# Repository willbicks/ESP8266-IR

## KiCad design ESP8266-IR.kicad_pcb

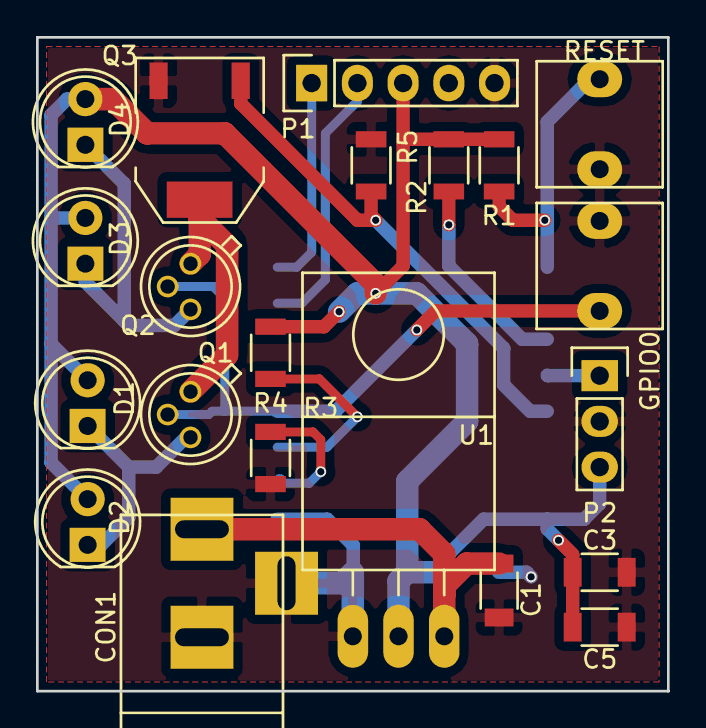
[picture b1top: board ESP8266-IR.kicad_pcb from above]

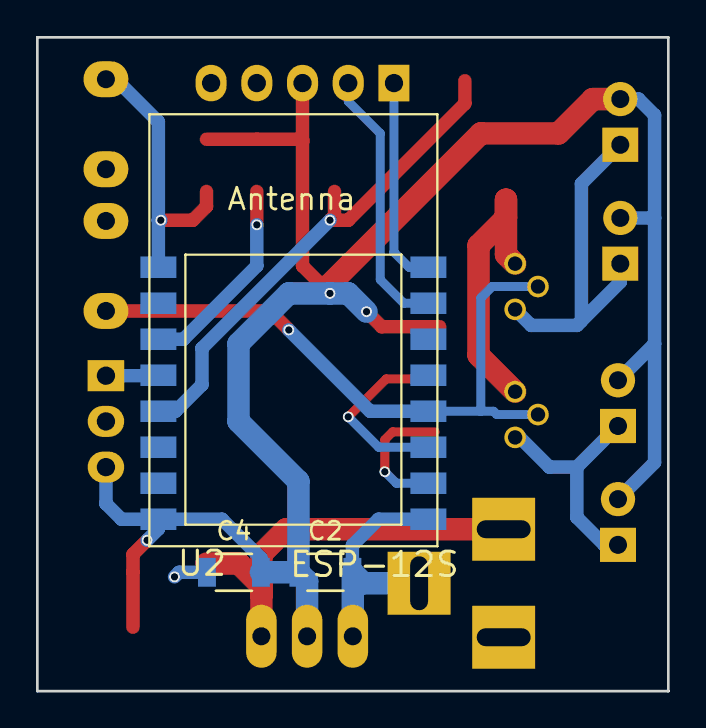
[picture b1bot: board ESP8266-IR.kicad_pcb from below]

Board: 2 copper layers, 35.1 x 36.3 mm, 24 parts (3 on the bottom side), 15 nets.

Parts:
C1, C2, C4: 10uF; C_1206
C3, C5: C; C_1206
CON1: BARREL_JACK
D1, D2, D3, D4: LED; LED-5MM
GPIO0: SW_PUSH; PushbuttonSquare2pin
P1: CONN_01X05; Pin_Header_Straight_1x05
P2: TSOP38238; Pin_Header_Straight_1x03
Q1, Q2: 2N2222A; TO-18_3Pin
Q3: Q_NMOS_GDS; SOT-223
R1, R2, R3, R4, R5: 10k; R_1206
RESET: SW_PUSH; PushbuttonSquare2pin
U1: LD1117S33TR; TO-220_Neutral123_Horizontal_LargePads
U2: ESP-12S; ESP-12

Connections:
+3V3: C2.1, C3.1, C4.2, C5.1, D1.2, D2.2, D3.2, D4.2, P1.3, P2.3, R1.1, R2.2, R3.1, U1.2, U2.8
/ESP_RST: R1.2, RESET.2, U2.1
/ESP_RXD: P1.2, U2.15
/ESP_TXD: P1.1, U2.16
/GPIO0: GPIO0.2, Q1.2, Q2.2, U2.12
/IR_EN: Q3.1, R5.1, U2.5
/IR_IN: P2.1, U2.4
/VIN: C1.1, CON1.1, U1.3
GND: C1.2, C2.2, C3.2, C4.1, C5.2, CON1.2, CON1.3, GPIO0.1, P1.5, P2.2, Q3.3, R4.2, R5.2, RESET.1, U1.1, U2.9
unnamed: D1.1, D2.1, Q1.3
unnamed: D3.1, D4.1, Q2.3
unnamed: Q1.1, Q2.1, Q3.2
unnamed: R2.1, U2.3
unnamed: R3.2, U2.11
unnamed: R4.1, U2.10

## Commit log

2016-12-10 Created schematic, added voltage regulation.
2016-12-11 Initial commit.
2016-12-15 Layout adjustments, inital sketch commit.
2016-12-15 Added modified SOT-223 for MOSFET.
2016-12-15 Removed ATTINY coprocessor.
2016-12-15 Changed footpints.
2016-12-24 Complete relayout, more smoothing, two layer design.
